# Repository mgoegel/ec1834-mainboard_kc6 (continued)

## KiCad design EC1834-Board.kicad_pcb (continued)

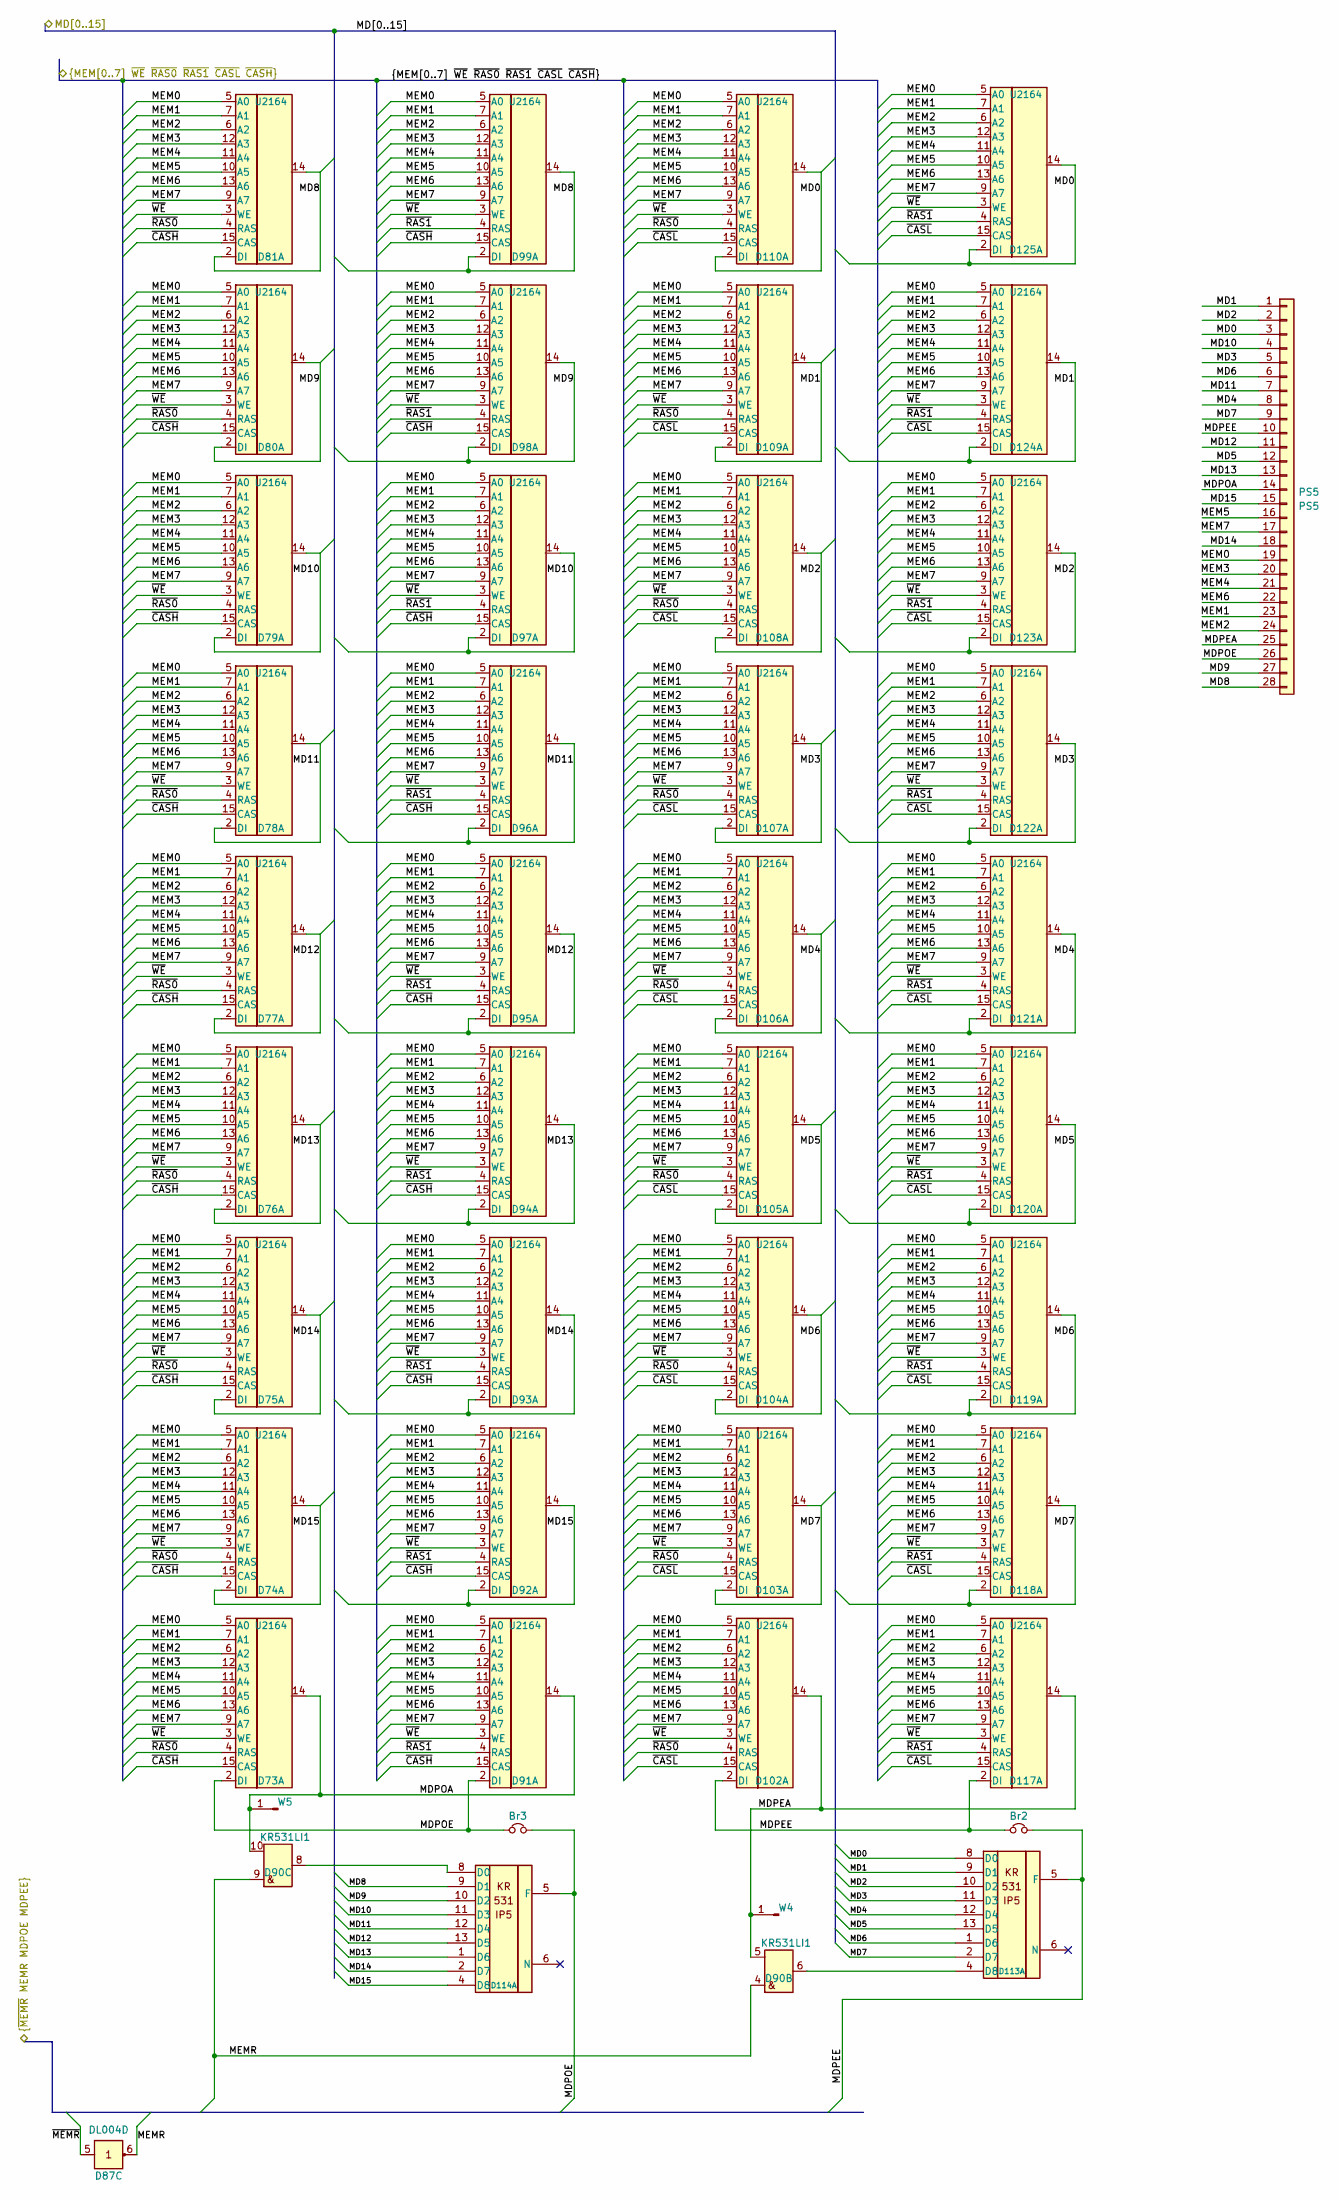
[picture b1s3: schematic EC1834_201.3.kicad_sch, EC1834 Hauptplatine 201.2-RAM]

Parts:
Br2: Br2; R_Axial_DIN0204_L3.6mm_D1.6mm_P7.62mm_Horizontal
Br3: Br3; R_Axial_DIN0204_L3.6mm_D1.6mm_P7.62mm_Horizontal
D73, D74, D75, D76, D77, D78, D79, D80, D81, D91, D92, D93, D94, D95, D96, D97, D98, D99, D102, D103, D104, D105, D106, D107, D108, D109, D110, D117, D118, D119, D120, D121, D122, D123, D124, D125: U2164; DIP-16_W7.62mm
D87: DL004D; DIP-14_W7.62mm
D90: KR531LI1; DIP-14_W7.62mm
D113, D114: KR531IP5; DIP-14_W7.62mm
PS5: PS5; Pruefstecker5
W4: W4; PinHeader_1x01_P2.54mm_Vertical
W5: W5; PinHeader_1x01_P2.54mm_Vertical

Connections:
/EC1834 201.1/MDPEE: Br2.1, Br2.2, D102.2 (DI), D113.5 (F), D117.2 (DI), PS5.10; also elsewhere on the board
/EC1834 201.1/MDPOE: Br3.1, Br3.2, D73.2 (DI), D91.2 (DI), D114.5 (F), PS5.26; also elsewhere on the board
/EC1834 201.1/MEMR: D87.6 (Y3), D90.4 (A2), D90.9 (A3); also elsewhere on the board
/EC1834 201.1/~MEMR: D87.5 (A3); also elsewhere on the board
/EC1834_201.3 RAM/MD0: D110.2 (DI), D110.14, D113.8 (D0), D125.2 (DI), D125.14, PS5.3; also elsewhere on the board
/EC1834_201.3 RAM/MD1: D109.2 (DI), D109.14, D113.9 (D1), D124.2 (DI), D124.14, PS5.1; also elsewhere on the board
/EC1834_201.3 RAM/MD2: D108.2 (DI), D108.14, D113.10 (D2), D123.2 (DI), D123.14, PS5.2; also elsewhere on the board
/EC1834_201.3 RAM/MD3: D107.2 (DI), D107.14, D113.11 (D3), D122.2 (DI), D122.14, PS5.5; also elsewhere on the board
/EC1834_201.3 RAM/MD4: D106.2 (DI), D106.14, D113.12 (D4), D121.2 (DI), D121.14, PS5.8; also elsewhere on the board
/EC1834_201.3 RAM/MD5: D105.2 (DI), D105.14, D113.13 (D5), D120.2 (DI), D120.14, PS5.12; also elsewhere on the board
/EC1834_201.3 RAM/MD6: D104.2 (DI), D104.14, D113.1 (D6), D119.2 (DI), D119.14, PS5.6; also elsewhere on the board
/EC1834_201.3 RAM/MD7: D103.2 (DI), D103.14, D113.2 (D7), D118.2 (DI), D118.14, PS5.9; also elsewhere on the board
/EC1834_201.3 RAM/MD8: D81.2 (DI), D81.14, D99.2 (DI), D99.14, D114.9 (D1), PS5.28; also elsewhere on the board
/EC1834_201.3 RAM/MD9: D80.2 (DI), D80.14, D98.2 (DI), D98.14, D114.10 (D2), PS5.27; also elsewhere on the board
/EC1834_201.3 RAM/MD10: D79.2 (DI), D79.14, D97.2 (DI), D97.14, D114.11 (D3), PS5.4; also elsewhere on the board
/EC1834_201.3 RAM/MD11: D78.2 (DI), D78.14, D96.2 (DI), D96.14, D114.12 (D4), PS5.7; also elsewhere on the board
/EC1834_201.3 RAM/MD12: D77.2 (DI), D77.14, D95.2 (DI), D95.14, D114.13 (D5), PS5.11; also elsewhere on the board
/EC1834_201.3 RAM/MD13: D76.2 (DI), D76.14, D94.2 (DI), D94.14, D114.1 (D6), PS5.13; also elsewhere on the board
/EC1834_201.3 RAM/MD14: D75.2 (DI), D75.14, D93.2 (DI), D93.14, D114.2 (D7), PS5.18; also elsewhere on the board
/EC1834_201.3 RAM/MD15: D74.2 (DI), D74.14, D92.2 (DI), D92.14, D114.4 (D8), PS5.15; also elsewhere on the board
/EC1834_201.3 RAM/MDPEA: D90.5 (B2), D102.14, D117.14, PS5.25, W4.1
/EC1834_201.3 RAM/MDPOA: D73.14, D90.10 (B3), D91.14, PS5.14, W5.1
/EC1834_201.3 RAM/MEM0: D73.5 (A0), D74.5 (A0), D75.5 (A0), D76.5 (A0), D77.5 (A0), D78.5 (A0), D79.5 (A0), D80.5 (A0), D81.5 (A0), D91.5 (A0), D92.5 (A0), D93.5 (A0), D94.5 (A0), D95.5 (A0), D96.5 (A0), D97.5 (A0), D98.5 (A0), D99.5 (A0), D102.5 (A0), D103.5 (A0), D104.5 (A0), D105.5 (A0), D106.5 (A0), D107.5 (A0), D108.5 (A0), D109.5 (A0), D110.5 (A0), D117.5 (A0), D118.5 (A0), D119.5 (A0), D120.5 (A0), D121.5 (A0), D122.5 (A0), D123.5 (A0), D124.5 (A0), D125.5 (A0), PS5.19
/EC1834_201.3 RAM/MEM1: D73.7 (A1), D74.7 (A1), D75.7 (A1), D76.7 (A1), D77.7 (A1), D78.7 (A1), D79.7 (A1), D80.7 (A1), D81.7 (A1), D91.7 (A1), D92.7 (A1), D93.7 (A1), D94.7 (A1), D95.7 (A1), D96.7 (A1), D97.7 (A1), D98.7 (A1), D99.7 (A1), D102.7 (A1), D103.7 (A1), D104.7 (A1), D105.7 (A1), D106.7 (A1), D107.7 (A1), D108.7 (A1), D109.7 (A1), D110.7 (A1), D117.7 (A1), D118.7 (A1), D119.7 (A1), D120.7 (A1), D121.7 (A1), D122.7 (A1), D123.7 (A1), D124.7 (A1), D125.7 (A1), PS5.23
/EC1834_201.3 RAM/MEM2: D73.6 (A2), D74.6 (A2), D75.6 (A2), D76.6 (A2), D77.6 (A2), D78.6 (A2), D79.6 (A2), D80.6 (A2), D81.6 (A2), D91.6 (A2), D92.6 (A2), D93.6 (A2), D94.6 (A2), D95.6 (A2), D96.6 (A2), D97.6 (A2), D98.6 (A2), D99.6 (A2), D102.6 (A2), D103.6 (A2), D104.6 (A2), D105.6 (A2), D106.6 (A2), D107.6 (A2), D108.6 (A2), D109.6 (A2), D110.6 (A2), D117.6 (A2), D118.6 (A2), D119.6 (A2), D120.6 (A2), D121.6 (A2), D122.6 (A2), D123.6 (A2), D124.6 (A2), D125.6 (A2), PS5.24
/EC1834_201.3 RAM/MEM3: D73.12 (A3), D74.12 (A3), D75.12 (A3), D76.12 (A3), D77.12 (A3), D78.12 (A3), D79.12 (A3), D80.12 (A3), D81.12 (A3), D91.12 (A3), D92.12 (A3), D93.12 (A3), D94.12 (A3), D95.12 (A3), D96.12 (A3), D97.12 (A3), D98.12 (A3), D99.12 (A3), D102.12 (A3), D103.12 (A3), D104.12 (A3), D105.12 (A3), D106.12 (A3), D107.12 (A3), D108.12 (A3), D109.12 (A3), D110.12 (A3), D117.12 (A3), D118.12 (A3), D119.12 (A3), D120.12 (A3), D121.12 (A3), D122.12 (A3), D123.12 (A3), D124.12 (A3), D125.12 (A3), PS5.20
/EC1834_201.3 RAM/MEM4: D73.11 (A4), D74.11 (A4), D75.11 (A4), D76.11 (A4), D77.11 (A4), D78.11 (A4), D79.11 (A4), D80.11 (A4), D81.11 (A4), D91.11 (A4), D92.11 (A4), D93.11 (A4), D94.11 (A4), D95.11 (A4), D96.11 (A4), D97.11 (A4), D98.11 (A4), D99.11 (A4), D102.11 (A4), D103.11 (A4), D104.11 (A4), D105.11 (A4), D106.11 (A4), D107.11 (A4), D108.11 (A4), D109.11 (A4), D110.11 (A4), D117.11 (A4), D118.11 (A4), D119.11 (A4), D120.11 (A4), D121.11 (A4), D122.11 (A4), D123.11 (A4), D124.11 (A4), D125.11 (A4), PS5.21
/EC1834_201.3 RAM/MEM5: D73.10 (A5), D74.10 (A5), D75.10 (A5), D76.10 (A5), D77.10 (A5), D78.10 (A5), D79.10 (A5), D80.10 (A5), D81.10 (A5), D91.10 (A5), D92.10 (A5), D93.10 (A5), D94.10 (A5), D95.10 (A5), D96.10 (A5), D97.10 (A5), D98.10 (A5), D99.10 (A5), D102.10 (A5), D103.10 (A5), D104.10 (A5), D105.10 (A5), D106.10 (A5), D107.10 (A5), D108.10 (A5), D109.10 (A5), D110.10 (A5), D117.10 (A5), D118.10 (A5), D119.10 (A5), D120.10 (A5), D121.10 (A5), D122.10 (A5), D123.10 (A5), D124.10 (A5), D125.10 (A5), PS5.16
/EC1834_201.3 RAM/MEM6: D73.13 (A6), D74.13 (A6), D75.13 (A6), D76.13 (A6), D77.13 (A6), D78.13 (A6), D79.13 (A6), D80.13 (A6), D81.13 (A6), D91.13 (A6), D92.13 (A6), D93.13 (A6), D94.13 (A6), D95.13 (A6), D96.13 (A6), D97.13 (A6), D98.13 (A6), D99.13 (A6), D102.13 (A6), D103.13 (A6), D104.13 (A6), D105.13 (A6), D106.13 (A6), D107.13 (A6), D108.13 (A6), D109.13 (A6), D110.13 (A6), D117.13 (A6), D118.13 (A6), D119.13 (A6), D120.13 (A6), D121.13 (A6), D122.13 (A6), D123.13 (A6), D124.13 (A6), D125.13 (A6), PS5.22
/EC1834_201.3 RAM/MEM7: D73.9 (A7), D74.9 (A7), D75.9 (A7), D76.9 (A7), D77.9 (A7), D78.9 (A7), D79.9 (A7), D80.9 (A7), D81.9 (A7), D91.9 (A7), D92.9 (A7), D93.9 (A7), D94.9 (A7), D95.9 (A7), D96.9 (A7), D97.9 (A7), D98.9 (A7), D99.9 (A7), D102.9 (A7), D103.9 (A7), D104.9 (A7), D105.9 (A7), D106.9 (A7), D107.9 (A7), D108.9 (A7), D109.9 (A7), D110.9 (A7), D117.9 (A7), D118.9 (A7), D119.9 (A7), D120.9 (A7), D121.9 (A7), D122.9 (A7), D123.9 (A7), D124.9 (A7), D125.9 (A7), PS5.17
/EC1834_201.3 RAM/~CASH: D73.15 (CAS), D74.15 (CAS), D75.15 (CAS), D76.15 (CAS), D77.15 (CAS), D78.15 (CAS), D79.15 (CAS), D80.15 (CAS), D81.15 (CAS), D91.15 (CAS), D92.15 (CAS), D93.15 (CAS), D94.15 (CAS), D95.15 (CAS), D96.15 (CAS), D97.15 (CAS), D98.15 (CAS), D99.15 (CAS); also elsewhere on the board
/EC1834_201.3 RAM/~CASL: D102.15 (CAS), D103.15 (CAS), D104.15 (CAS), D105.15 (CAS), D106.15 (CAS), D107.15 (CAS), D108.15 (CAS), D109.15 (CAS), D110.15 (CAS), D117.15 (CAS), D118.15 (CAS), D119.15 (CAS), D120.15 (CAS), D121.15 (CAS), D122.15 (CAS), D123.15 (CAS), D124.15 (CAS), D125.15 (CAS); also elsewhere on the board
/EC1834_201.3 RAM/~RAS0: D73.4 (RAS), D74.4 (RAS), D75.4 (RAS), D76.4 (RAS), D77.4 (RAS), D78.4 (RAS), D79.4 (RAS), D80.4 (RAS), D81.4 (RAS), D102.4 (RAS), D103.4 (RAS), D104.4 (RAS), D105.4 (RAS), D106.4 (RAS), D107.4 (RAS), D108.4 (RAS), D109.4 (RAS), D110.4 (RAS); also elsewhere on the board
/EC1834_201.3 RAM/~RAS1: D91.4 (RAS), D92.4 (RAS), D93.4 (RAS), D94.4 (RAS), D95.4 (RAS), D96.4 (RAS), D97.4 (RAS), D98.4 (RAS), D99.4 (RAS), D117.4 (RAS), D118.4 (RAS), D119.4 (RAS), D120.4 (RAS), D121.4 (RAS), D122.4 (RAS), D123.4 (RAS), D124.4 (RAS), D125.4 (RAS); also elsewhere on the board
/EC1834_201.3 RAM/~WE: D73.3 (WE), D74.3 (WE), D75.3 (WE), D76.3 (WE), D77.3 (WE), D78.3 (WE), D79.3 (WE), D80.3 (WE), D81.3 (WE), D91.3 (WE), D92.3 (WE), D93.3 (WE), D94.3 (WE), D95.3 (WE), D96.3 (WE), D97.3 (WE), D98.3 (WE), D99.3 (WE), D102.3 (WE), D103.3 (WE), D104.3 (WE), D105.3 (WE), D106.3 (WE), D107.3 (WE), D108.3 (WE), D109.3 (WE), D110.3 (WE), D117.3 (WE), D118.3 (WE), D119.3 (WE), D120.3 (WE), D121.3 (WE), D122.3 (WE), D123.3 (WE), D124.3 (WE), D125.3 (WE); also elsewhere on the board
unnamed: D90.6 (Y2), D113.4 (D8)
unnamed: D90.8 (Y3), D114.8 (D0)

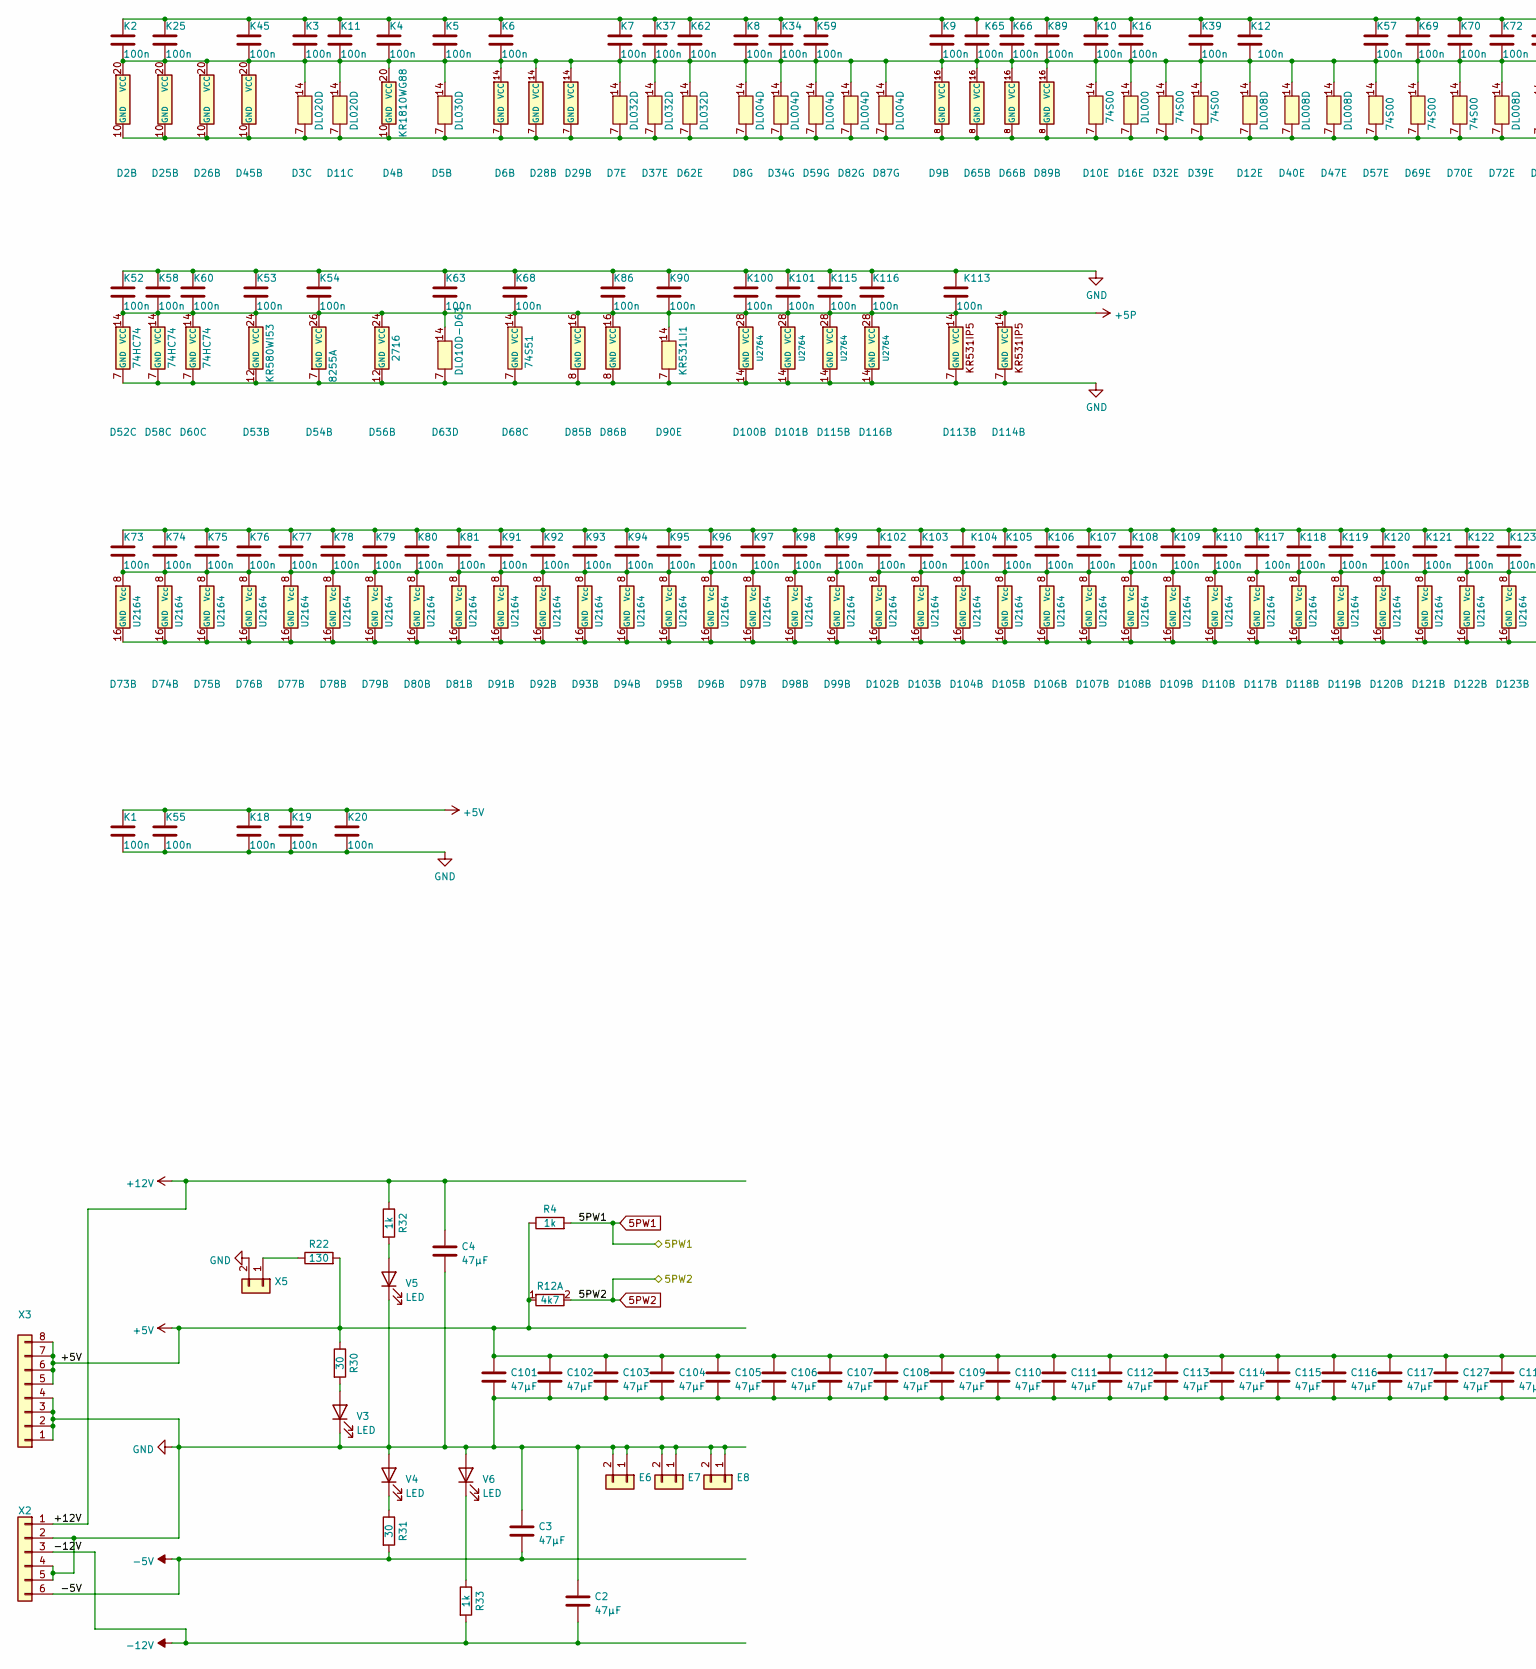
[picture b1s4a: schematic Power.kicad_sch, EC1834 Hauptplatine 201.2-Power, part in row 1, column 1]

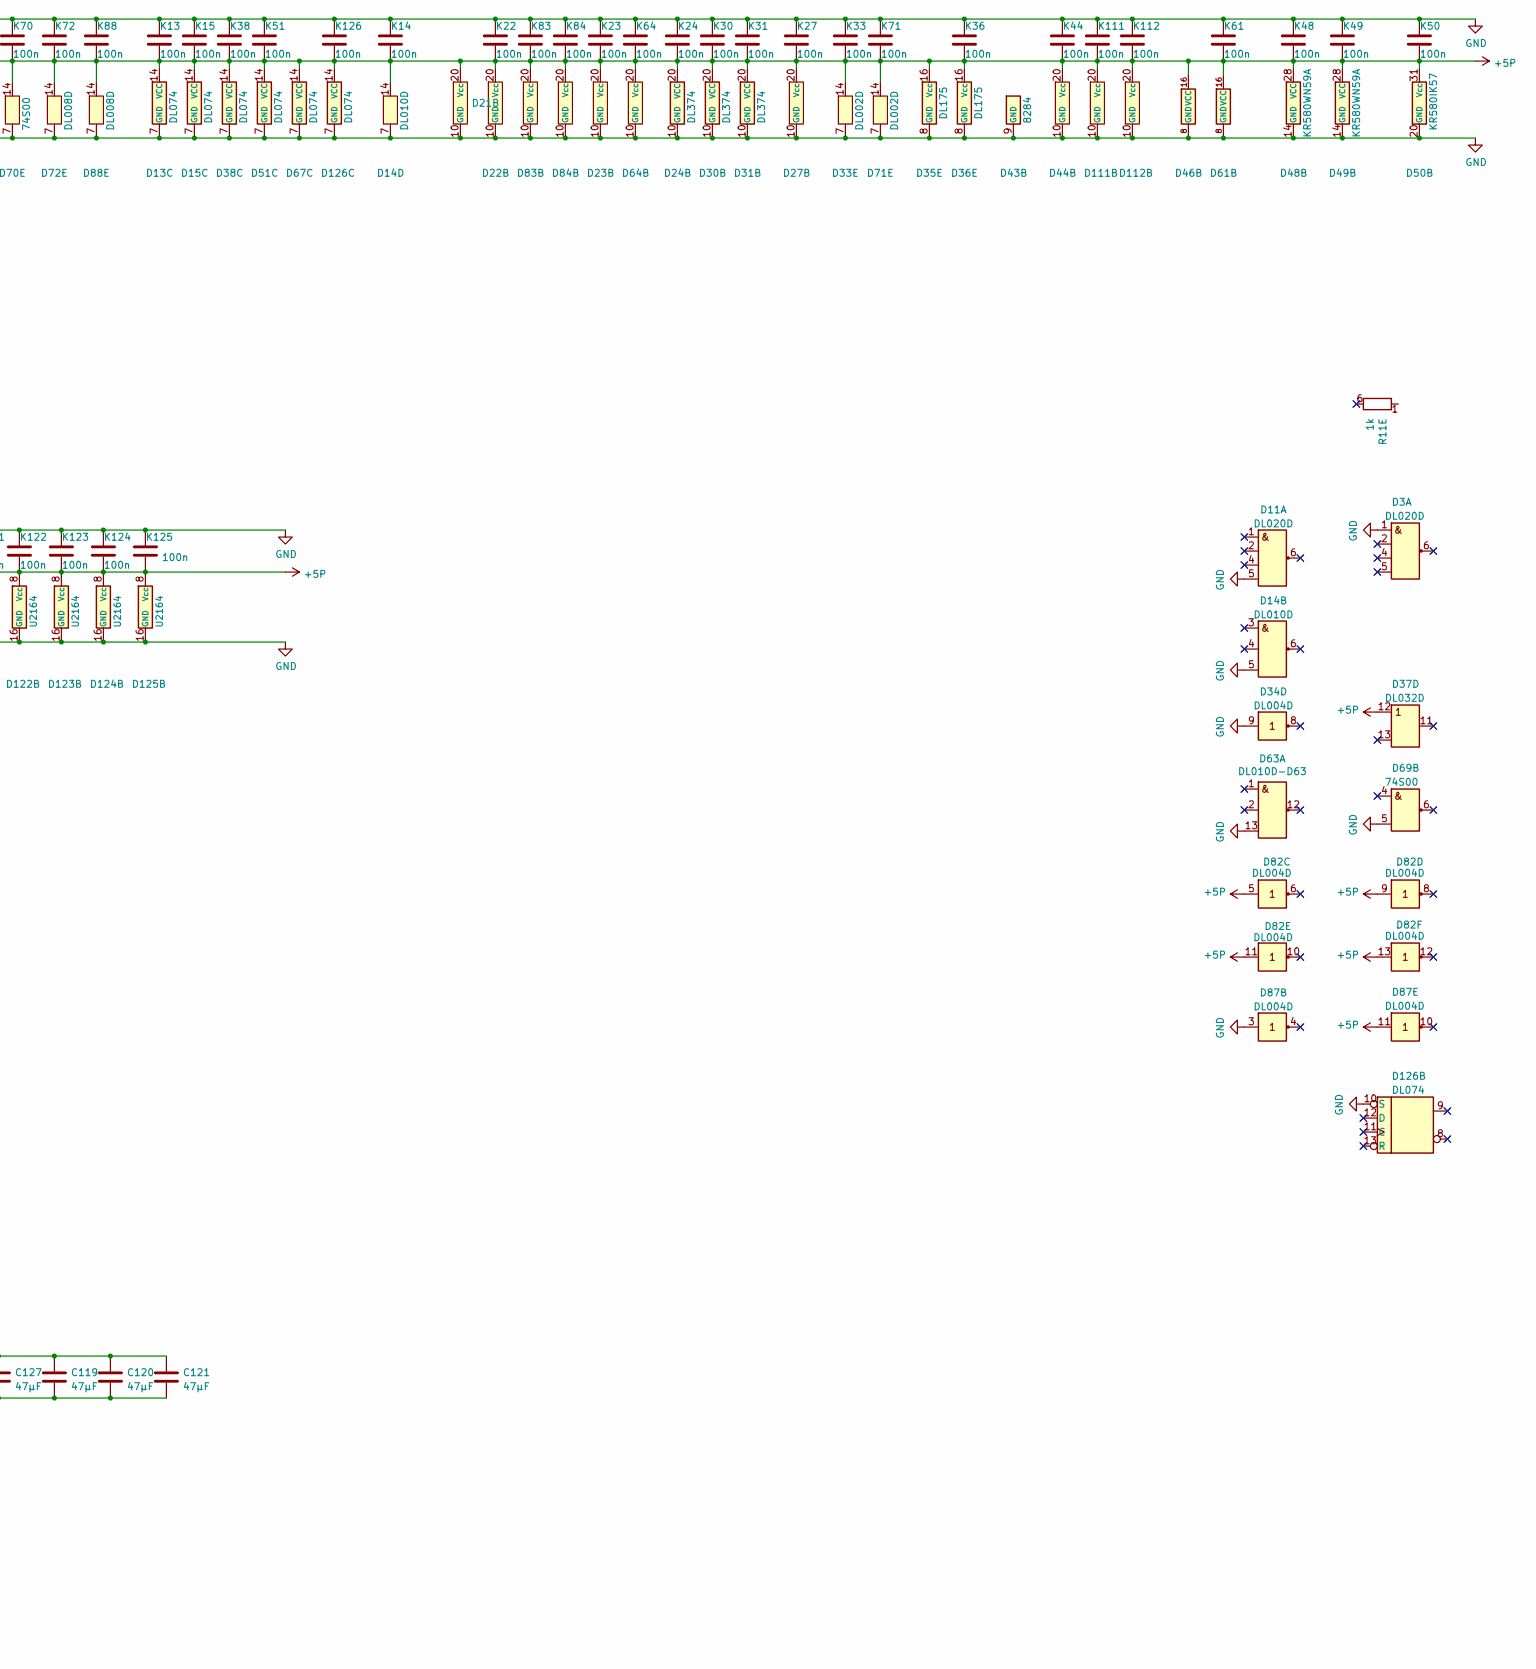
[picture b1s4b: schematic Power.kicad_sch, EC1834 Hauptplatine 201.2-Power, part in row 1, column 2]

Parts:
C2, C3, C4, C101, C102, C103, C104, C105, C106, C107, C108, C109, C110, C111, C112, C113, C114, C115, C116, C117, C119, C120, C121, C127: 47µF; CP_Radial_D5.0mm_P2.50mm
D2, D25, D26, D45: DS8282; DIP-20_W7.62mm
D3, D11: DL020D; DIP-14_W7.62mm
D4: KR1810WG88; DIP-20_W7.62mm
D5: DL030D; DIP-14_W7.62mm
D6, D28, D29: DL295; DIP-14_W7.62mm
D7, D37, D62: DL032D; DIP-14_W7.62mm
D8, D34, D59, D82, D87: DL004D; DIP-14_W7.62mm
D9, D65, D66, D89: DS8205; DIP-16_W7.62mm
D10, D32, D39, D57, D69, D70: 74S00; DIP-14_W7.62mm
D12, D40, D47, D72, D88: DL008D; DIP-14_W7.62mm
D13, D15, D38, D51, D67, D126: DL074; DIP-14_W7.62mm
D14: DL010D; DIP-14_W7.62mm
D16: DL000; DIP-14_W7.62mm
D21, D44, D111, D112: DS8286D-D111; DIP-20_W7.62mm
D22, D83, D84: DS8286D; DIP-20_W7.62mm
D23, D64: DS8286D-D23; DIP-20_W7.62mm
D24, D30, D31: DL374; DIP-20_W7.62mm
D27: DS8286D-D27; DIP-20_W7.62mm
D33, D71: DL002D; DIP-14_W7.62mm
D35, D36: DL175; DIP-16_W7.62mm
D43: 8284; DIP-18_W7.62mm
D46, D61: DS8216; DIP-16_W7.62mm
D48, D49: KR580WN59A; DIP-28_W15.24mm
D50: KR580IK57; DIP-40_W15.24mm
D52, D58, D60: 74HC74; DIP-14_W7.62mm
D53: KR580WI53; DIP-24_W15.24mm
D54: 8255A; DIP-40_W15.24mm
D56: 2716; DIP-24_W15.24mm
D63: DL010D-D63; DIP-14_W7.62mm
D68: 74S51; DIP-14_W7.62mm
D73, D74, D75, D76, D77, D78, D79, D80, D81, D91, D92, D93, D94, D95, D96, D97, D98, D99, D102, D103, D104, D105, D106, D107, D108, D109, D110, D117, D118, D119, D120, D121, D122, D123, D124, D125: U2164; DIP-16_W7.62mm
D85, D86: KR531KP11; DIP-16_W7.62mm
D90: KR531LI1; DIP-14_W7.62mm
D100, D101, D115, D116: U2764; DIP-28_W15.24mm
D113, D114: KR531IP5; DIP-14_W7.62mm
E6, E7, E8: Conn_01x02; PinHeader_1x02_P2.54mm_Vertical
K1, K2, K3, K4, K5, K6, K7, K8, K9, K10, K11, K12, K13, K14, K15, K16, K18, K19, K20, K22, K23, K24, K25, K27, K30, K31, K33, K34, K36, K37, K38, K39, K44, K45, K48, K49, K50, K51, K52, K53, K54, K55, K57, K58, K59, K60, K61, K62, K63, K64, K65, K66, K68, K69, K70, K71, K72, K73, K74, K75, K76, K77, K78, K79, K80, K81, K83, K84, K86, K88, K89, K90, K91, K92, K93, K94, K95, K96, K97, K98, K99, K100, K101, K102, K103, K104, K105, K106, K107, K108, K109, K110, K111, K112, K113, K115, K116, K117, K118, K119, K120, K121, K122, K123, K124, K125, K126: 100n; C_Disc_D4.3mm_W1.9mm_P5.00mm
R4, R32, R33: 1k; R_Axial_L9.0mm_D1.8mm_P12.70mm_Horizontal
R11: 1k; R_Array_SIP6
R12: 4k7; R_Array_SIP10
R22: 130; R_Axial_L9.0mm_D1.8mm_P12.70mm_Horizontal
R30, R31: 30; R_Axial_L9.0mm_D1.8mm_P12.70mm_Horizontal
V3, V4, V5, V6: LED; LED_D3.0mm
X2: Conn_01x06; TerminalBlock_RND_205-00236_1x06_P5.08mm_Horizontal
X3: Conn_01x08; TerminalBlock_RND_205-00238_1x08_P5.08mm_Horizontal
X5: PowerLED; PinHeader_1x02_P2.54mm_Vertical

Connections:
5PW1: R4.2; also elsewhere on the board
5PW2: R12.2 (R1.2); also elsewhere on the board
+5P: D2.20 (VCC), D3.14 (Vcc), D4.20 (VCC), D5.14 (Vcc), D6.14 (VCC), D7.14 (Vcc), D8.14 (Vcc), D9.16 (VCC), D10.14 (Vcc), D11.14 (Vcc), D12.14 (Vcc), D13.14 (VCC), D14.14 (Vcc), D15.14 (VCC), D16.14 (Vcc), D21.20 (Vcc), D22.20 (Vcc), D23.20 (Vcc), D24.20 (VCC), D25.20 (VCC), D26.20 (VCC), D27.20 (Vcc), D28.14 (VCC), D29.14 (VCC), D30.20 (VCC), D31.20 (VCC), D32.14 (Vcc), D33.14 (Vcc), D34.14 (Vcc), D35.16 (Vcc), D36.16 (Vcc), D37.12 (A4), D37.14 (Vcc), D38.14 (VCC), D39.14 (Vcc), D40.14 (Vcc), D44.20 (Vcc), D45.20 (VCC), D46.16 (VCC), D47.14 (Vcc), D48.28 (VCC), D49.28 (VCC), D50.31 (Vcc), D51.14 (VCC), D52.14 (VCC), D53.24 (VCC), D54.26 (VCC), D56.24 (VCC), D57.14 (Vcc), D58.14 (VCC), D59.14 (Vcc), D60.14 (VCC), D61.16 (VCC), D62.14 (Vcc), D63.14 (Vcc), D64.20 (Vcc), D65.16 (VCC), D66.16 (VCC), D67.14 (VCC), D68.14 (VCC), D69.14 (Vcc), D70.14 (Vcc), D71.14 (Vcc), D72.14 (Vcc), D73.8 (Vcc), D74.8 (Vcc), D75.8 (Vcc), D76.8 (Vcc), D77.8 (Vcc), D78.8 (Vcc), D79.8 (Vcc), D80.8 (Vcc), D81.8 (Vcc), D82.5 (A3), D82.9 (A4), D82.11 (A5), D82.13 (A6), D82.14 (Vcc), D83.20 (Vcc), D84.20 (Vcc), D85.16 (VCC), D86.16 (VCC), D87.11 (A5), D87.14 (Vcc), D88.14 (Vcc), D89.16 (VCC), D90.14 (Vcc), D91.8 (Vcc), D92.8 (Vcc), D93.8 (Vcc), D94.8 (Vcc), D95.8 (Vcc), D96.8 (Vcc), D97.8 (Vcc), D98.8 (Vcc), D99.8 (Vcc), D100.28 (VCC), D101.28 (VCC), D102.8 (Vcc), D103.8 (Vcc), D104.8 (Vcc), D105.8 (Vcc), D106.8 (Vcc), D107.8 (Vcc), D108.8 (Vcc), D109.8 (Vcc), D110.8 (Vcc), D111.20 (Vcc), D112.20 (Vcc), D113.14 (VCC), D114.14 (VCC), D115.28 (VCC), D116.28 (VCC), D117.8 (Vcc), D118.8 (Vcc), D119.8 (Vcc), D120.8 (Vcc), D121.8 (Vcc), D122.8 (Vcc), D123.8 (Vcc), D124.8 (Vcc), D125.8 (Vcc), D126.14 (VCC), K2.2, K3.2, K4.2, K5.2, K6.2, K7.2, K8.2, K9.2, K10.2, K11.2, K12.2, K13.2, K14.2, K15.2, K16.2, K22.2, K23.2, K24.2, K25.2, K27.2, K30.2, K31.2, K33.2, K34.2, K36.2, K37.2, K38.2, K39.2, K44.2, K45.2, K48.2, K49.2, K50.2, K51.2, K52.2, K53.2, K54.2, K57.2, K58.2, K59.2, K60.2, K61.2, K62.2, K63.2, K64.2, K65.2, K66.2, K68.2, K69.2, K70.2, K71.2, K72.2, K73.2, K74.2, K75.2, K76.2, K77.2, K78.2, K79.2, K80.2, K81.2, K83.2, K84.2, K86.2, K88.2, K89.2, K90.2, K91.2, K92.2, K93.2, K94.2, K95.2, K96.2, K97.2, K98.2, K99.2, K100.2, K101.2, K102.2, K103.2, K104.2, K105.2, K106.2, K107.2, K108.2, K109.2, K110.2, K111.2, K112.2, K113.2, K115.2, K116.2, K117.2, K118.2, K119.2, K120.2, K121.2, K122.2, K123.2, K124.2, K125.2, K126.2
+5V: C101.1, C102.1, C103.1, C104.1, C105.1, C106.1, C107.1, C108.1, C109.1, C110.1, C111.1, C112.1, C113.1, C114.1, C115.1, C116.1, C117.1, C119.1, C120.1, C121.1, C127.1, K1.1, K18.1, K19.1, K20.1, K55.1, R4.1, R12.1 (R1.1), R22.2, R30.1, X3.5 (+5V), X3.6 (+5V), X3.7 (+5V), X3.8 (+5V); also elsewhere on the board
+12V: C4.1, R32.1, X2.1; also elsewhere on the board
-5V: C3.2, R31.2, X2.6; also elsewhere on the board
-12V: C2.2, R33.2, X2.3; also elsewhere on the board
GND: C2.1, C3.1, C4.2, C101.2, C102.2, C103.2, C104.2, C105.2, C106.2, C107.2, C108.2, C109.2, C110.2, C111.2, C112.2, C113.2, C114.2, C115.2, C116.2, C117.2, C119.2, C120.2, C121.2, C127.2, D2.10 (GND), D3.1 (A1), D3.7 (GND), D4.10 (GND), D5.7 (GND), D6.7 (GND), D7.7 (GND), D8.7 (GND), D9.8 (GND), D10.7 (GND), D11.5 (D1), D11.7 (GND), D12.7 (GND), D13.7 (GND), D14.5 (C2), D14.7 (GND), D15.7 (GND), D16.7 (GND), D21.10 (GND), D22.10 (GND), D23.10 (GND), D24.10 (GND), D25.10 (GND), D26.10 (GND), D27.10 (GND), D28.7 (GND), D29.7 (GND), D30.10 (GND), D31.10 (GND), D32.7 (GND), D33.7 (GND), D34.7 (GND), D34.9 (A4), D35.8 (GND), D36.8 (GND), D37.7 (GND), D38.7 (GND), D39.7 (GND), D40.7 (GND), D43.9 (GND), D44.10 (GND), D45.10 (GND), D46.8 (GND), D47.7 (GND), D48.14 (GND), D49.14 (GND), D50.20 (GND), D51.7 (GND), D52.7 (GND), D53.12 (GND), D54.7 (GND), D56.12 (GND), D57.7 (GND), D58.7 (GND), D59.7 (GND), D60.7 (GND), D61.8 (GND), D62.7 (GND), D63.7 (GND), D63.13 (C1), D64.10 (GND), D65.8 (GND), D66.8 (GND), D67.7 (GND), D68.7 (GND), D69.5 (B2), D69.7 (GND), D70.7 (GND), D71.7 (GND), D72.7 (GND), D73.16 (GND), D74.16 (GND), D75.16 (GND), D76.16 (GND), D77.16 (GND), D78.16 (GND), D79.16 (GND), D80.16 (GND), D81.16 (GND), D82.7 (GND), D83.10 (GND), D84.10 (GND), D85.8 (GND), D86.8 (GND), D87.3 (A2), D87.7 (GND), D88.7 (GND), D89.8 (GND), D90.7 (GND), D91.16 (GND), D92.16 (GND), D93.16 (GND), D94.16 (GND), D95.16 (GND), D96.16 (GND), D97.16 (GND), D98.16 (GND), D99.16 (GND), D100.14 (GND), D101.14 (GND), D102.16 (GND), D103.16 (GND), D104.16 (GND), D105.16 (GND), D106.16 (GND), D107.16 (GND), D108.16 (GND), D109.16 (GND), D110.16 (GND), D111.10 (GND), D112.10 (GND), D113.7 (GND), D114.7 (GND), D115.14 (GND), D116.14 (GND), D117.16 (GND), D118.16 (GND), D119.16 (GND), D120.16 (GND), D121.16 (GND), D122.16 (GND), D123.16 (GND), D124.16 (GND), D125.16 (GND), D126.7 (GND), D126.10 (S), E6.1, E6.2, E7.1, E7.2, E8.1, E8.2, K1.2, K2.1, K3.1, K4.1, K5.1, K6.1, K7.1, K8.1, K9.1, K10.1, K11.1, K12.1, K13.1, K14.1, K15.1, K16.1, K18.2, K19.2, K20.2, K22.1, K23.1, K24.1, K25.1, K27.1, K30.1, K31.1, K33.1, K34.1, K36.1, K37.1, K38.1, K39.1, K44.1, K45.1, K48.1, K49.1, K50.1, K51.1, K52.1, K53.1, K54.1, K55.2, K57.1, K58.1, K59.1, K60.1, K61.1, K62.1, K63.1, K64.1, K65.1, K66.1, K68.1, K69.1, K70.1, K71.1, K72.1, K73.1, K74.1, K75.1, K76.1, K77.1, K78.1, K79.1, K80.1, K81.1, K83.1, K84.1, K86.1, K88.1, K89.1, K90.1, K91.1, K92.1, K93.1, K94.1, K95.1, K96.1, K97.1, K98.1, K99.1, K100.1, K101.1, K102.1, K103.1, K104.1, K105.1, K106.1, K107.1, K108.1, K109.1, K110.1, K111.1, K112.1, K113.1, K115.1, K116.1, K117.1, K118.1, K119.1, K120.1, K121.1, K122.1, K123.1, K124.1, K125.1, K126.1, V3.1 (K), V4.2 (A), V5.1 (K), V6.2 (A), X2.2, X2.4, X2.5, X3.1 (GND), X3.2 (GND), X3.3 (GND), X3.4 (GND), X5.2; also elsewhere on the board
unnamed: R22.1, X5.1
unnamed: R30.2, V3.2 (A)
unnamed: R31.1, V4.1 (K)
unnamed: R32.2, V5.2 (A)
unnamed: R33.1, V6.1 (K)
